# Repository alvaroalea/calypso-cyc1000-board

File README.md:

# The calypso board project

Calypso is just another middleboard based on the Arrow/Trenz cyc1000 board. This was born as a personal project to experiment with such board as it was delivered by Arrow Electronics as part of their European "Jump Start" Program for FPGAs.

THIS FORK is only to try to got a cheap way to order pcb with SMD components solder, please refer to the original project for any:

https://github.com/teiram/calypso-cyc1000-board

## Prices:
### 5 QTY
|Type of build: |  |  /5    |
|----|----|----|
|Only PCB                                                          |   1,89€+1,43€ =    4€ |  1€ |
|All smd (71)(but no 1 resistor, transistors, PCM5102, usb socket) |  43,25€+17,43€ =  61€ |  12€ |
|Only basic smd components + Diodes (62)(no 1C, 9R, 2Q, PCM, usb ) |  19,63€+17.xx€ =  38€ |  8€ |
|Only basic smd components (52)(previos - diodes)                  |  15,97€+16,68€ =  33€ |  7€ |

### 2QTY + 3 PCB
|Type of build: |  |  /2    |
|----|----|----|
|All smd (71)(but no 1 resistor, transistors, PCM5102, usb socket) | 40,75€+16,68€=57€-3€=55€ |  27€ |

### 20 QTY
|Type of build: |  |  /20    |
|----|----|----|
|All smd (71)(but no 1 resistor, transistors, PCM5102, usb socket) |  82,93€+42,74€ = 126€ |  6.5€ |
|Only basic smd components + Diodes  (62)(no 1C, 9R, 2Q, PCM, usb ) |  51,09€+41,41€ =  93€ |  5€ |

### 10 QTY
|Type of build:                                                     |                      |  /10    |
|-------------------------------------------------------------------|----------------------|---------|
|All smd (71)(but no 1 resistor, transistors, PCM5102, usb socket)  | 53,17€+26,89€ =  80€ |  8€     |
|Only basic smd components + Diodes  (62)(no 1C, 9R, 2Q, PCM, usb ) | 27,19€+26,06€ =  54€ |  5.5€   |

# Original Doc:

The board takes ideas and design from other existing hobbyist project boards, embracing the following design principles:
- Doesn't try to support multiple FPGAs and/or MCUs. it's based on the CYC1000 board and an R2040 as MCU
- Follows the Mist ideas about IO, being the MCU the hub for most IO needs. This is convenient since the CYC1000 doesn't expose a big number of pins to the outside world.
- Tries to be compatible to some extent with Mist IO, therefore exposing a SPI bus mastered by the MCU to the FPGA, and the well known select signals CONF_DATA0, MIST_SS2, MIST_SS3 and MIST_SS4. This should ease the task of porting cores from Mist or boards with a similar design.
# Features
- VGA444 output via an standard VGA DB15 connector
- Optional AV output via a RCA connector. Both VGA and AV share FPGA pins.
- DB9 connector for a joystick with up to 2 fire buttons
- SD card
- Two PS/2 connectors
- Power button
- Reset button
- Ear input
- I2S audio output
- Mini USB for main power supply
- AUX connector for extension, exposing free pins in both the Cyc1000 and the RP2040.

# Pinout
As of preview version 0.2 this is the pinout description

# Support firmware
Firmware for the RP2040 MCU is so far a fork of zxmicrojack for RP2040 based Mist (https://github.com/ZXMicroJack/mist-firmware-rp2040) modified for calypso. The aim is to develop a specific and more minimalistic firmware since the current one was used mostly for board validation purposes. The forked firmware can be found here: https://github.com/teiram/mist-firmware-rp2040 

> [!NOTE]  
> I'm happy to share that we have now an oficial firmware for the board. It's still in a preliminary stage but should support most of the needed feature for Mist compatibility > and you can find it here: https://github.com/teiram/calypso-firmware/

# Disclaimer
This is a personal project I started with the support of the RetroWiki FPGA Dev community (thank you guys). There is no aim for commercial benefit neither I will provide any warranty or support beyond what my free time allows for. Feel free to build the board for your personal use, or a limited batch of units for your pals. It works for me, but I tested it with a very limited set of hardware, so your milleage may vary.
Enjoy ;)

# Errata, issues
## Version 0.3
- Fixed Q2 footprint and updated values for C16 and C17. This version is so far untested, but since Q2 issue was fixed manually without need ro reroute the board again, there are good chances it's safe to use.
  
## Version 0.2
- Q2 footprint is wrong. The schematic shows a BC547 but a SMD BC847 was intended. Unfortunately the pinout doesn´t match. So in case you want to use the composite video output you need to adjust it accordingly. A BC847 can be installed by rotating it 90º counterclockwise, what makes soldering a bit trickier but it can be done.
- The board supports RP2040 clones known as YD-2040 by VCC-GND studio. An official RP2040 won´t work completely due to:
  - The SWD header in the official RP2040 has 3 pins instead of 4 pins, so you cannot take advantage of the SWD/UART connector but you can still attach your SWD device directly to the RP2040.
  - YD-2040 exposes GPIO 23 on pin 37, which is not the case for in the official RP2040. Unfortunately GPIO23 is used for one of the DB9 joystick directions, and therefore a DB9 joystick won't work properly with an official RP2040
  - The YD-2040 doesn´t expose VBUS on the breakboard pins, therefore USB devices can only be used if they are self-powered or connected through a self-powered USB hub. The official RP2040 exposes VBUS and therefore it would be possible to power the bus without the need of a powered hub. But since the design was based on the YD-2040 there is no provision for that. This might be addressed in future releases.

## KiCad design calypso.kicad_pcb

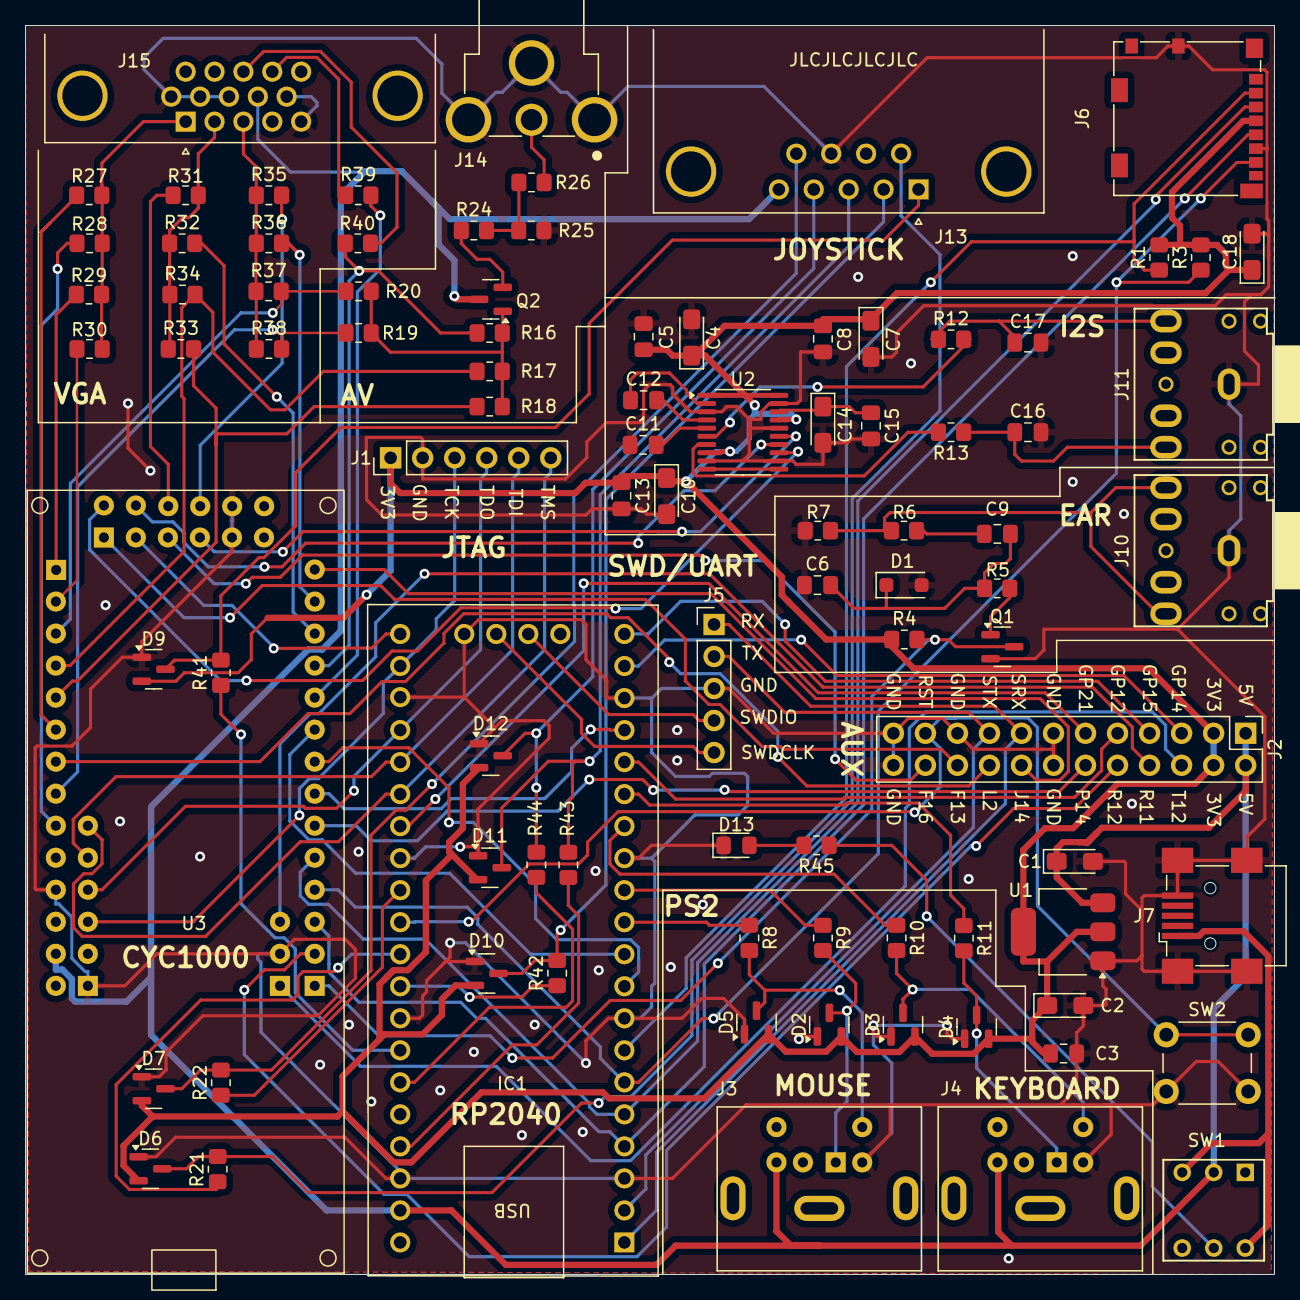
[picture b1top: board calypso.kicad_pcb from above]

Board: 2 copper layers, 99.1 x 99.1 mm, 91 parts (0 on the bottom side), 95 nets.

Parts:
C1, C2, C4, C7, C10, C14, C18: 10uF; CP_EIA-3216-12_Kemet-S_Pad1.58x1.35mm_HandSolder
C3, C5, C8, C9, C13, C15: 100nF; C_0805_2012Metric_Pad1.18x1.45mm_HandSolder
C6: 10nF; C_0805_2012Metric_Pad1.18x1.45mm_HandSolder
C11, C12: 2.2uF; C_0805_2012Metric_Pad1.18x1.45mm_HandSolder
C16, C17: 2.2nF; C_0805_2012Metric_Pad1.18x1.45mm_HandSolder
D1: 1N4148; D_SOD-123F
D2, D3, D4, D5, D6, D7, D9, D10, D11, D12: BAT54S; SOT-23
D13: LED; LED_0805_2012Metric_Pad1.15x1.40mm_HandSolder
IC1: RP2040_breakout; RP2040-Breakout_swd
J1: Conn_01x06; PinHeader_1x06_P2.54mm_Vertical
J2: Conn_02x12_Odd_Even; PinHeader_2x12_P2.54mm_Vertical
J3, J4: Mini-DIN-6; Connector_Mini-DIN_Female_6Pin_2rows
J5: Conn_01x05; PinHeader_1x05_P2.54mm_Vertical
J6: Micro_SD_Card; microSD_HC_Molex_104031-0811
J7: USB_B_Mini; USB_Mini-B_Wuerth_65100516121_Horizontal
J10, J11: AudioJack3; pj307
J13: Joy; DSUB-9_Male_Horizontal_P2.77x2.84mm_EdgePinOffset9.90mm_Hou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
J14: Video Out; CUI_RCJ-013
J15: DB15_Female_HighDensity; DSUB-15-HD_Female_Horizontal_P2.29x1.98mm_EdgePinOffset3.03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
Q1, Q2: BC846; SOT-23
R1, R3, R5, R7, R17: 10K; R_0805_2012Metric_Pad1.20x1.40mm_HandSolder
R4, R28, R32, R36, R45: 1K; R_0805_2012Metric_Pad1.20x1.40mm_HandSolder
R6, R8, R9, R10, R11, R21, R22, R27, R31, R35, R41, R42, R43, R44: 510; R_0805_2012Metric_Pad1.20x1.40mm_HandSolder
R12, R13: 470; R_0805_2012Metric_Pad1.20x1.40mm_HandSolder
R16: 810; R_0805_2012Metric_Pad1.20x1.40mm_HandSolder
R18: 4K7; R_0805_2012Metric_Pad1.20x1.40mm_HandSolder
R19: 2K2; R_0805_2012Metric_Pad1.20x1.40mm_HandSolder
R20: 1K2; R_0805_2012Metric_Pad1.20x1.40mm_HandSolder
R24: 33; R_0805_2012Metric_Pad1.20x1.40mm_HandSolder
R25: 100; R_0805_2012Metric_Pad1.20x1.40mm_HandSolder
R26: 51; R_0805_2012Metric_Pad1.20x1.40mm_HandSolder
R29, R33, R37: 2K; R_0805_2012Metric_Pad1.20x1.40mm_HandSolder
R30, R34, R38: 3K9; R_0805_2012Metric_Pad1.20x1.40mm_HandSolder
R39, R40: 270; R_0805_2012Metric_Pad1.20x1.40mm_HandSolder
SW1: SWDPDTBLUE; SW_PUSH_x2
SW2: SW_Push; SW_PUSH_6mm_H4.3mm
U1: AMS1117-3.3; SOT-223-3_TabPin2
U2: PCM5102; TSSOP-20_4.4x6.5mm_P0.65mm
U3: CYC1000; cyc1000

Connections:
+3.3VP: C2.1, C3.2, C4.1, C5.1, C7.1, C8.1, C10.1, C13.1, C18.1, D2.2, D3.2, D4.2, D5.2, D6.2, D7.2, D9.2, D10.2, D11.2, D12.2, J1.1, J2.3, J2.4, J6.4 (VDD), R1.2, R3.2, R4.1, U1.2 (VO), U2.1 (CPVDD), U2.8 (AVDD), U2.17 (XSMT), U2.20 (DVDD)
+5V: C1.1, IC1.39 (Vin), J2.1, J2.2, J3.4, J4.4, J13.5, J15.9, Q2.3 (C), SW1.2 (NO_1), U1.3 (VI), U3.2.13 (VIN)
BCK: U2.13 (BCK), U3.6.7 (PIO05)
C10_B16: R31.2, U3.6.9 (PIO07)
C10_C15: U2.14 (DIN), U3.6.8 (PIO06)
C10_C16: R35.2, U3.6.10 (PIO08)
C10_D16: U2.15 (LRCK), U3.6.4 (PIO04)
C10_F13: J2.20, U3.6.1 (PIO01)
C10_F15: IC1.21 (GP16), U3.6.2 (PIO02)
C10_F16: J2.22, U3.6.3 (PIO03)
C10_J1: R17.2, R34.2, U3.2.4 (D9)
C10_J2: R18.2, R33.2, U3.2.5 (D10)
C10_J14: J2.16, U3.1.14 (D5)
C10_K2: R27.2, U3.2.6 (D11)
C10_K15: R32.2, U3.1.12 (D3)
C10_K16: R36.2, U3.1.13 (D4)
C10_L2: J2.18, U3.2.7 (D12)
C10_L15: R39.2, U3.1.10 (D1)
C10_L16: R16.2, R40.2, U3.1.11 (D2)
C10_N1: R30.2, U3.2.2 (D7)
C10_N2: R29.2, U3.2.1 (D6)
C10_N16: IC1.10 (GP7), U3.1.9 (D0)
C10_P1: R19.2, R38.2, U3.2.8 (D13)
C10_P2: R20.2, R37.2, U3.2.3 (D8)
C10_P11: Q1.3 (C), R4.2, U3.1.1 (AREF)
C10_P14: J2.12, U3.1.6 (AIN4)
C10_R1: R28.2, U3.2.9 (D14)
C10_R11: J2.8, U3.3.3 (AIN7)
C10_R12: J2.10, U3.1.2 (AIN0)
C10_R13: IC1.6 (GP4), J6.7 (DAT0), R3.1, U3.1.4 (AIN2)
C10_R14: IC1.17 (GP13), U3.1.7 (AIN5)
C10_T12: J2.6, U3.3.1 (AIN)
C10_T13: IC1.4 (GP2), J6.5 (CLK), U3.1.3 (AIN1)
C10_T14: IC1.5 (GP3), J6.3 (CMD), U3.1.5 (AIN3)
C10_T15: IC1.9 (GP6), U3.1.8 (AIN6)
GND: C1.2, C2.2, C3.1, C4.2, C5.2, C6.1, C7.2, C8.2, C10.2, C11.1, C13.2, C14.2, C15.2, C16.2, C17.2, C18.2, D1.2 (A), D2.1, D3.1, D4.1, D5.1, D6.1, D7.1, D9.1, D10.1, D11.1, D12.1, D13.1 (K), IC1.3 (GND), IC1.8 (GND), IC1.13 (GND), IC1.18 (GND), IC1.23 (GND), IC1.28 (GND), IC1.33 (GND), IC1.38 (GND), IC1.44 (GND), J1.2, J2.13, J2.14, J2.19, J2.23, J2.24, J3.3, J4.3, J5.3, J6.6 (VSS), J6.9 (SHIELD), J7.5 (GND), J7.6 (Shield), J10.S, J11.S, J13.8, J14.1A (1), J14.1B (1), J14.1C (1), J15.5, J15.6, J15.7, J15.8, J15.10, Q1.2 (E), R7.2, R25.2, SW2.2, U1.1 (GND), U2.3 (CPGND), U2.9 (AGND), U2.12 (SCK), U2.16 (FMT), U2.19 (DGND), U3.2.11 (GND), U3.3.2 (GND), U3.4.1 (GND), U3.6.5 (GND), U3.6.11 (GND)
IN_5V: J7.1 (VBUS), SW1.3 (C_1), SW1.6 (C_2)
JOY_DOWN: D10.3, J13.2, R42.2
JOY_FIRE1: D6.3, J13.6, R21.2
JOY_FIRE2: D7.3, J13.9, R22.2
JOY_LEFT: D11.3, J13.3, R43.2
JOY_RIGHT: D12.3, J13.4, R44.2
JOY_UP: D9.3, J13.1, R41.2
unnamed: C9.2, R6.1
unnamed: C16.1, J11.R, R13.1
unnamed: C17.1, J11.T, R12.1
unnamed: C6.2, C9.1, D1.1 (K), R5.2
unnamed: D2.3, J3.1, R9.2
unnamed: D3.3, J4.5, R10.2
unnamed: D4.3, J4.1, R11.2
unnamed: D5.3, J3.5, R8.2
unnamed: D13.2 (A), R45.2
unnamed: J10.R, J10.T, R6.2, R7.1
unnamed: J14.2, R26.1
unnamed: J15.1, R27.1, R28.1, R29.1, R30.1
unnamed: J15.2, R31.1, R32.1, R33.1, R34.1
unnamed: J15.3, R35.1, R36.1, R37.1, R38.1
unnamed: J15.13, R40.1
unnamed: J15.14, R39.1
unnamed: Q1.1 (B), R5.1
unnamed: Q2.1 (B), R16.1, R17.1, R18.1, R19.1, R20.1
unnamed: Q2.2 (E), R24.1
unnamed: R24.2, R25.1, R26.2
unnamed: R45.1, SW1.5 (NO_2)
unnamed: C12.2, U2.4 (CAPM)
unnamed: C12.1, U2.2 (CAPP)
unnamed: U2.10 (DEMP), U2.11 (FLT)
unnamed: C14.1, C15.1, U2.18 (LDOO)
unnamed: R12.2, U2.6 (OUTL)
unnamed: R13.2, U2.7 (OUTR)
unnamed: C11.2, U2.5 (VNEG)
PS2_K_CLK: IC1.14 (GP10), R10.1
PS2_K_DAT: IC1.15 (GP11), R11.1
PS2_M_CLK: IC1.11 (GP8), R8.1
PS2_M_DAT: IC1.12 (GP9), R9.1
RP_AUX0: IC1.19 (GP14), J2.5
RP_AUX1: IC1.20 (GP15), J2.7
RP_AUX2: IC1.16 (GP12), J2.9
RP_AUX3: IC1.27 (GP21), J2.11
RP_GP0: IC1.1 (GP0), J2.15, J5.1
RP_GP1: IC1.2 (GP1), J2.17, J5.2
RP_GP5: IC1.7 (GP5), J6.2 (DAT3/CD), R1.1
RP_GP17: IC1.22 (GP17), J1.3, U3.4.3 (TCK)
RP_GP18: IC1.24 (GP18), J1.4, U3.4.4 (TDO)
RP_GP19: IC1.25 (GP19), J1.5, U3.4.5 (TDI)
RP_GP20: IC1.26 (GP20), J1.6, U3.4.6 (TMS)
RP_GP22: IC1.29 (GP22), R22.1
RP_GP23: IC1.37 (GP23), R43.1
RP_GP26: IC1.31 (GP26), R21.1
RP_GP27: IC1.32 (GP27), R42.1
RP_GP28: IC1.34 (GP28), R41.1
RP_GP29: IC1.35 (GP29), R44.1
RP_RESET: IC1.30 (RUN), J2.21, SW2.1
RP_SWDCLK: IC1.43 (SWDCLK), J5.5
RP_SWDIO: IC1.42 (SWDIO), J5.4

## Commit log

2024-11-13 clarification
2024-11-13 test
2024-11-14 initial simulation of prices
2024-11-19 add PDF of schematics
